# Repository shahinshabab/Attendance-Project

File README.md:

# Office fingerprint attendance

This folder is the project workspace for an **ESP32 development board (ESP-WROOM-32), R307 UART fingerprint sensor, and 1.8″ ST7735 SPI TFT display**, with a DS3231 clock. Open `Attendance.code-workspace` in VS Code or open this folder directly.

The ESP32 is the implemented board. A standard Raspberry Pi Pico has no built-in Wi-Fi and needs different firmware; the supplied ESP32 firmware must not be flashed to a Pico. Pico W is a separate Wi-Fi-capable alternative, also requiring a port.

## Your deployed server

The dashboard/API is live at **https://attendance.shahinanalytics.com**, deployed through SSH alias `Attendance-Server`. Enter this computer's `ADMIN_API_KEY` value from `.env` in the dashboard. HTTPS, authentication, and automatic service startup have been checked. See [server details](docs/SERVER.md).

The board runs in **Wi-Fi mode** and talks to that server directly (see Connection modes below). The office Wi-Fi and fingerprint enrollment are both managed from the dashboard.

The USB connection on COM3 was verified and attendance firmware was uploaded after a full original-flash backup. Event storage was initialized and verified. The sensor (1000-slot capacity) and OLED (0x3C) were detected after shared-ground correction, but subsequent checks showed intermittent/missing communication; full power-cycle and wiring inspection are pending. Staff member Shabab (EMP001) exists on the server, but fingerprint enrollment has not succeeded and no slot is assigned. The steps below also cover running an optional local development server and provisioning another board. Do not reinitialize storage during routine firmware updates.

## Start here

1. Read [the wiring guide](docs/WIRING.md) and open [the labelled wiring diagram](docs/wiring.png) ([editable SVG](docs/wiring.svg)). Wire with USB unplugged. Use GPIO numbers, not physical header positions.
2. In PowerShell, from this folder, run:

   ```powershell
   .\scripts\setup.ps1
   .\scripts\start-server.ps1
   ```

   If your shell blocks scripts, run a command with `powershell -ExecutionPolicy Bypass -File .\scripts\setup.ps1` (process-specific; no permanent system policy change needed). Setup creates `.venv`, installs dependencies, generates independent random admin/device keys in `.env`, and copies the firmware configuration. Both secret files are git-ignored.
3. Open **http://127.0.0.1:8765**. Open `.env` locally, copy the `ADMIN_API_KEY` value into the dashboard, and click Connect. Do not share that key.
4. Connect the ESP32 development board with a **USB data cable**. In a second PowerShell window:

   ```powershell
   .\scripts\device.ps1 list
   .\scripts\device.ps1 build
   .\scripts\device.ps1 upload -Port COM3
   # FIRST INSTALL ONLY: creates the event filesystem; erases pending device scans.
   .\scripts\device.ps1 init-storage -Port COM3
   .\scripts\device.ps1 status -Port COM3
   ```

   Your board was detected as **Silicon Labs CP210x, COM3** during setup. Confirm it with `list` each time; Windows can change the port number. Do not choose a Bluetooth COM port. Close any serial monitor before uploading or opening the USB bridge. Upload replaces the board's current program. If uploading stalls at Connecting, hold BOOT, tap EN, then release BOOT when writing starts. Do not run `init-storage` during normal updates; pending scans survive ordinary firmware uploads when the partition layout is unchanged.
5. Create a staff member in the dashboard, for example `EMP001`. Enroll their fingerprint into a fresh slot:

   ```powershell
   .\scripts\device.ps1 enroll -Port COM3 -Slot 1
   ```

   Follow the display/terminal prompts: place finger, remove, place the same finger again. Enrollment takes place on the sensor; it does not create a server staff record. Assign device `office-01`, slot `1`, to `EMP001` in the dashboard. Remove the finger before starting attendance. Verify that a second enrollment into an occupied slot is refused on your particular sensor before enrolling the office.
6. Start the USB bridge:

   ```powershell
   .\scripts\device.ps1 bridge -Port COM3
   ```

   Scan, then click Refresh in the dashboard. The display's **Verified** means the finger matched and the scan is saved on the device; the terminal's **Saved** means the server accepted it. There is no IN/OUT button: the server decides IN or OUT from each person's scans that day (see [operations](docs/OPERATIONS.md)).

## Connection modes

**USB to this computer:** the ESP32 uses USB serial for enrollment and attendance. `tools/device.py` synchronizes the clock and forwards queued events. The local server and bridge both need to run. The computer can also forward to your internet server:

```powershell
.\scripts\device.ps1 bridge -Port COM3 -Server https://attendance.your-domain.example
```

Use the same device ID and device key on this computer and the remote server. The bridge never uses the admin key and validates normal HTTPS certificates.

**Standalone Wi-Fi to server (current setup):** the scanner connects straight to https://attendance.shahinanalytics.com without this computer. Office Wi-Fi is entered in the dashboard (Scanner & Wi-Fi). If it stops working, turn on a phone hotspot with the fallback name/password built into the firmware; the scanner connects through it, picks up the new office Wi-Fi from the dashboard, and switches back. No firmware change is needed. Enroll staff from the dashboard (Enroll a fingerprint): the scanner shows their name and the slot is assigned automatically. USB stays available for maintenance commands. Do not run the USB attendance bridge for a Wi-Fi board. See [server setup](docs/SERVER.md) and [operations](docs/OPERATIONS.md).

## Project layout

| Path | Purpose |
| --- | --- |
| `firmware/` | PlatformIO Arduino ESP32 firmware and hardware configuration |
| `backend/` | FastAPI service, SQLite database, and local dashboard |
| `tools/device.py` | USB bridge and physical enrollment/maintenance commands |
| `tools/firmware_config.py` | Writes the Wi-Fi-mode `config.h` (device key, server URL, root CAs, fallback hotspot) |
| `scripts/` | Windows setup, build, upload, and start commands |
| `docs/` | Wiring diagram, deployment notes, API and operating limits |
| `tests/` | API authentication, retries, date handling, and bridge acknowledgment tests |
| `.env` | Local server keys/configuration, excluded from Git |
| `data/` | Local database, excluded from Git |

Run checks with `.\.venv\Scripts\python.exe -m pytest -q`. The firmware dependencies and ESP32 platform are pinned in `platformio.ini`. Python installation versions are recorded in `requirements-lock.txt` after local verification; install that file to reproduce the tested environment.

This is a working project foundation for hardware commissioning. Hardware operation, fingerprint compatibility, and internet deployment must be verified with your actual board, sensor, display, and server before office use. See [operating notes](docs/OPERATIONS.md) for clock, queue, enrollment, and reporting limits.

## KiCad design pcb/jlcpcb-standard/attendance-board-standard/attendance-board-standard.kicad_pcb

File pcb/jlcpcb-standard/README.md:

# Standard-PCBA JLCPCB variant (ESP32 placed by JLCPCB)

Same circuit, 70 x 150 mm outline, layout and GPIO map as the other boards. It uses the Economic variant's
part choices (`../jlcpcb-economic`), and JLCPCB also places the ESP32 module U1. The module
(ESP32-WROOM-32E-N4, C701341) is **Standard-only** at JLCPCB, so this board must be ordered with
**Standard PCBA**. Its ground pad is the normal library footprint (no hand-solder holes).

| Ref | Part | Note |
| --- | --- | --- |
| U1 | C701341 ESP32-WROOM-32E-N4 | placed by JLCPCB (Standard PCBA) |
| C1, C3 | C2836436 470 uF 35 V 10 x 10.2 mm | |
| LED2, LED4, LED5 | C2297 KT-0805G green (Basic) | |
| D2 | C19077408 BZT52C10 SOD-123 | |
| L2 | rotated 180 degrees | so the boost switch node routes |

You hand-solder (see `production/hand-solder.csv`): on the front the headers J5 (display), J9 (programming,
optional) and J11 (R307); on the back BT1 (CR2032 holder), J3 (LiPo) and J7 (tamper). Standard PCBA can also
assemble the back side, but that doubles the setup and stencil fees for three easy parts.

## Files

| Path | What |
| --- | --- |
| `generator/` | Copy of `../jlcpcb-economic/generator` with U1 placed (`design.HAND` empty) |
| `attendance-board-standard/` | KiCad project, schematic PDF, DRC report |
| `production/` (git-ignored) | `attendance-board-standard-gerbers.zip`, `bom.csv`, `cpl.csv`, `hand-solder.csv`, renders |

## Ordering

PCB Assembly -> **Standard**, top side only; upload `bom.csv` and `cpl.csv`; check rotations in the preview.

## Cost estimate (JLCPCB price page, updated 2026-10-22)

Standard PCBA: $25.56 setup, $8.21 stencil, $1.53 feeder loading for every BOM line (42 here), fixtures $16.42
(1-29 boards) or $24.63 (30-99), $3.58 hand-soldering labour for J1/J8, $0.0016 per SMT joint, plus parts
(about $11.20 per board with the ESP32). A handling fee of at least $14.93 may be added. Excludes the bare PCB
and shipping.

| Boards | Standard (this board) | Economic + ESP32 soldered by you (`../jlcpcb-economic`) |
| --- | --- | --- |
| 5 | ~ $177 (up to ~ $192 with handling fee) | ~ $121 |
| 10 | ~ $236 | ~ $180 |
| 30 | ~ $480 | ~ $414 |

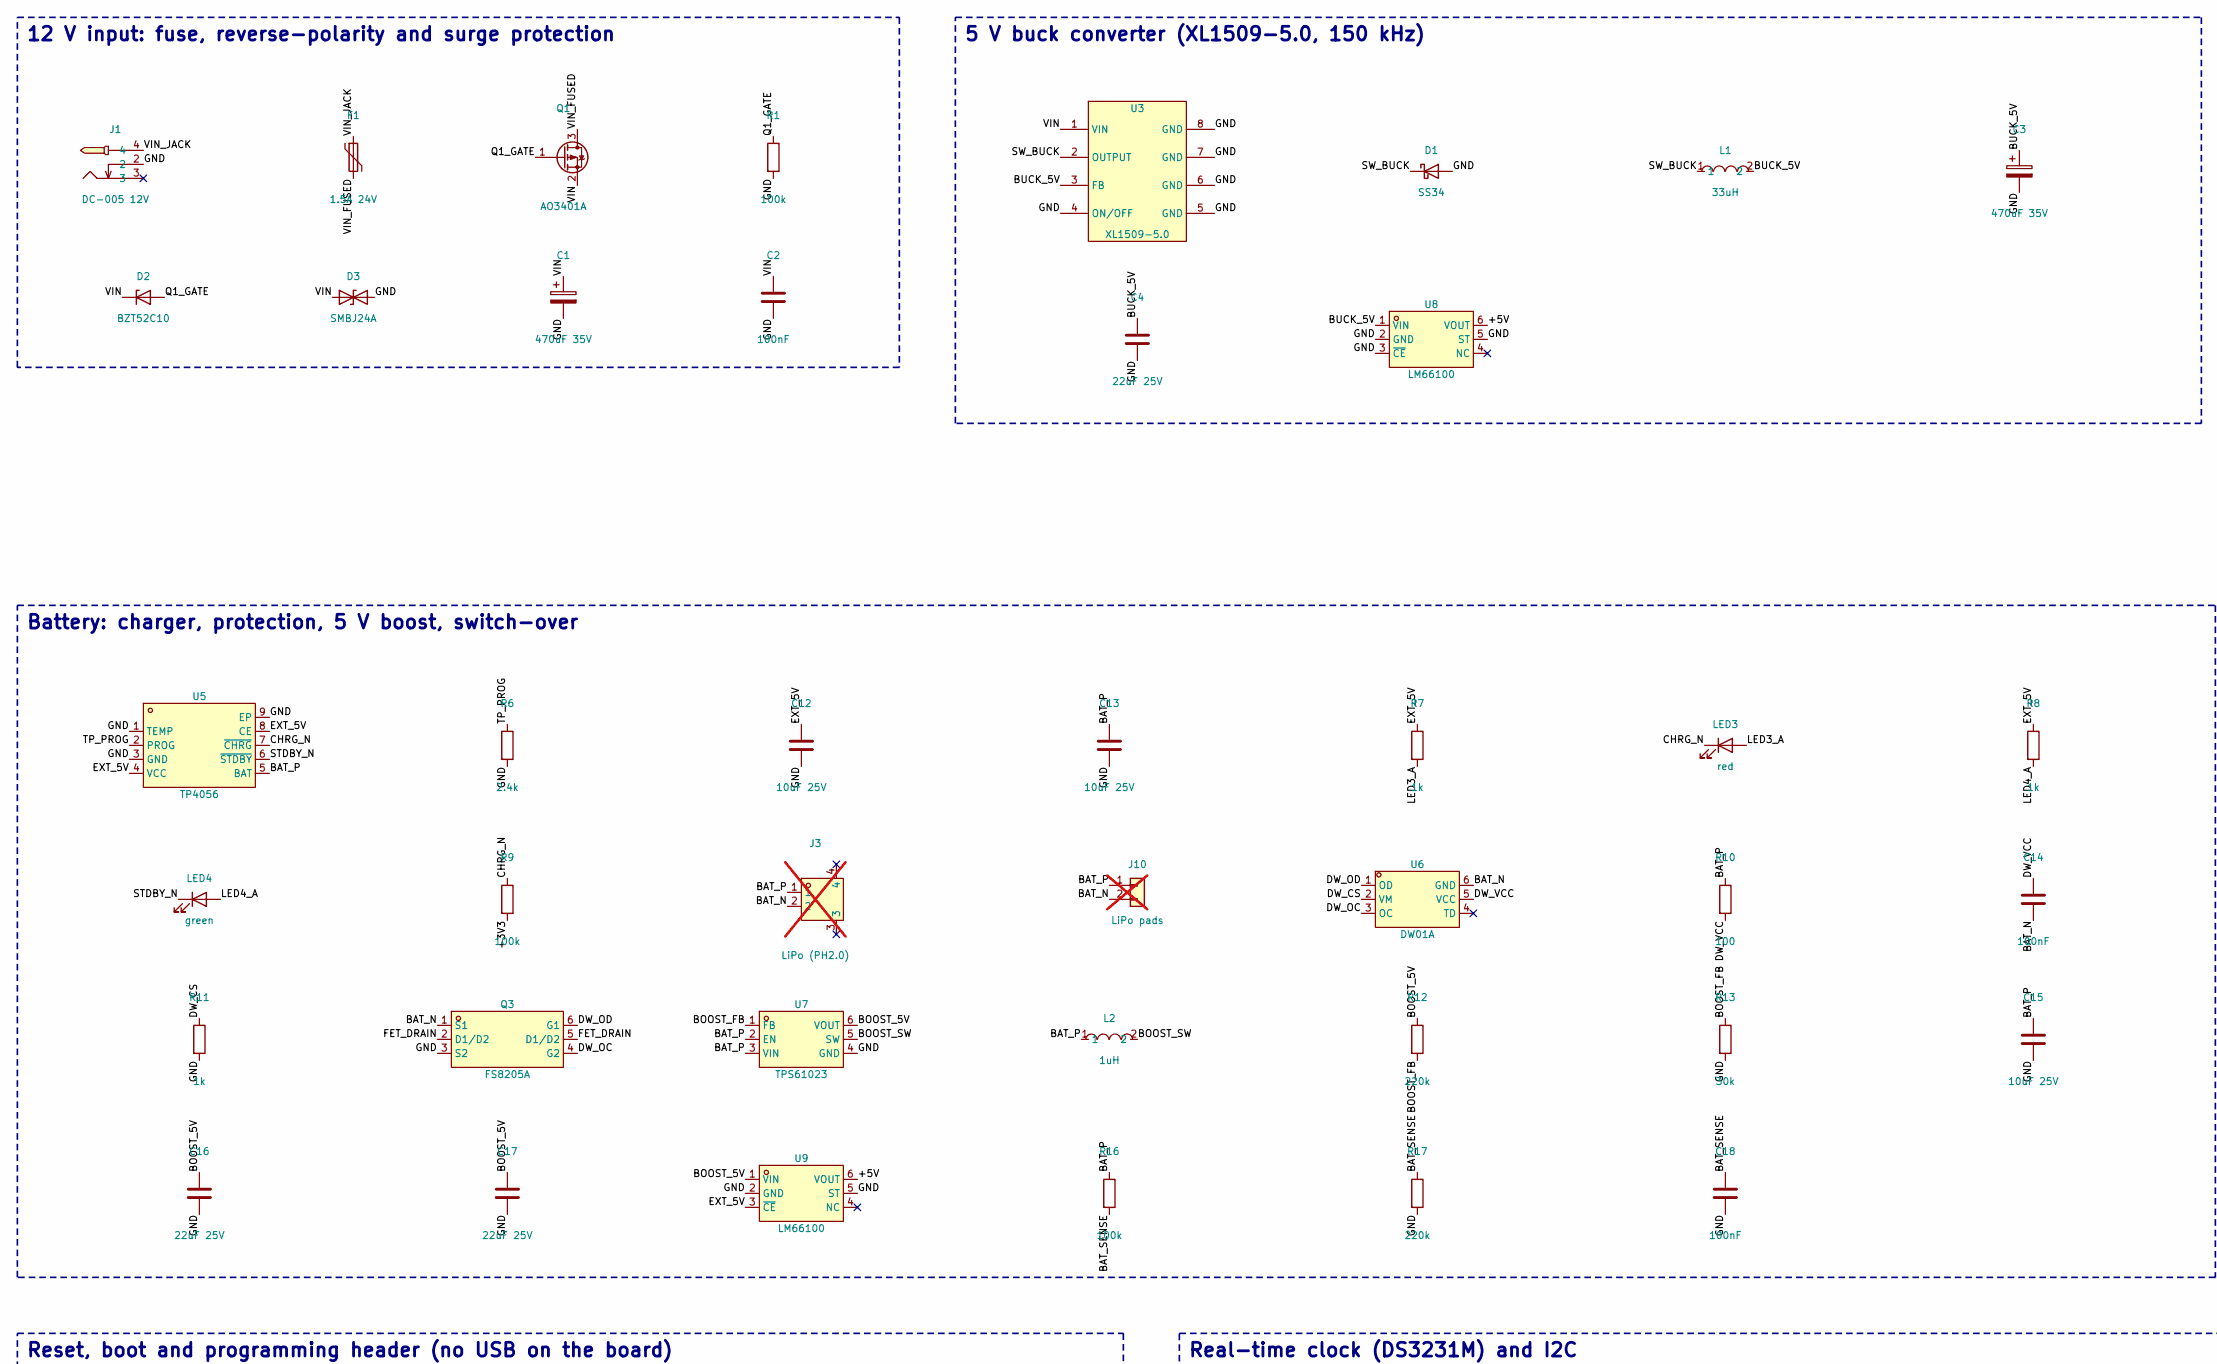
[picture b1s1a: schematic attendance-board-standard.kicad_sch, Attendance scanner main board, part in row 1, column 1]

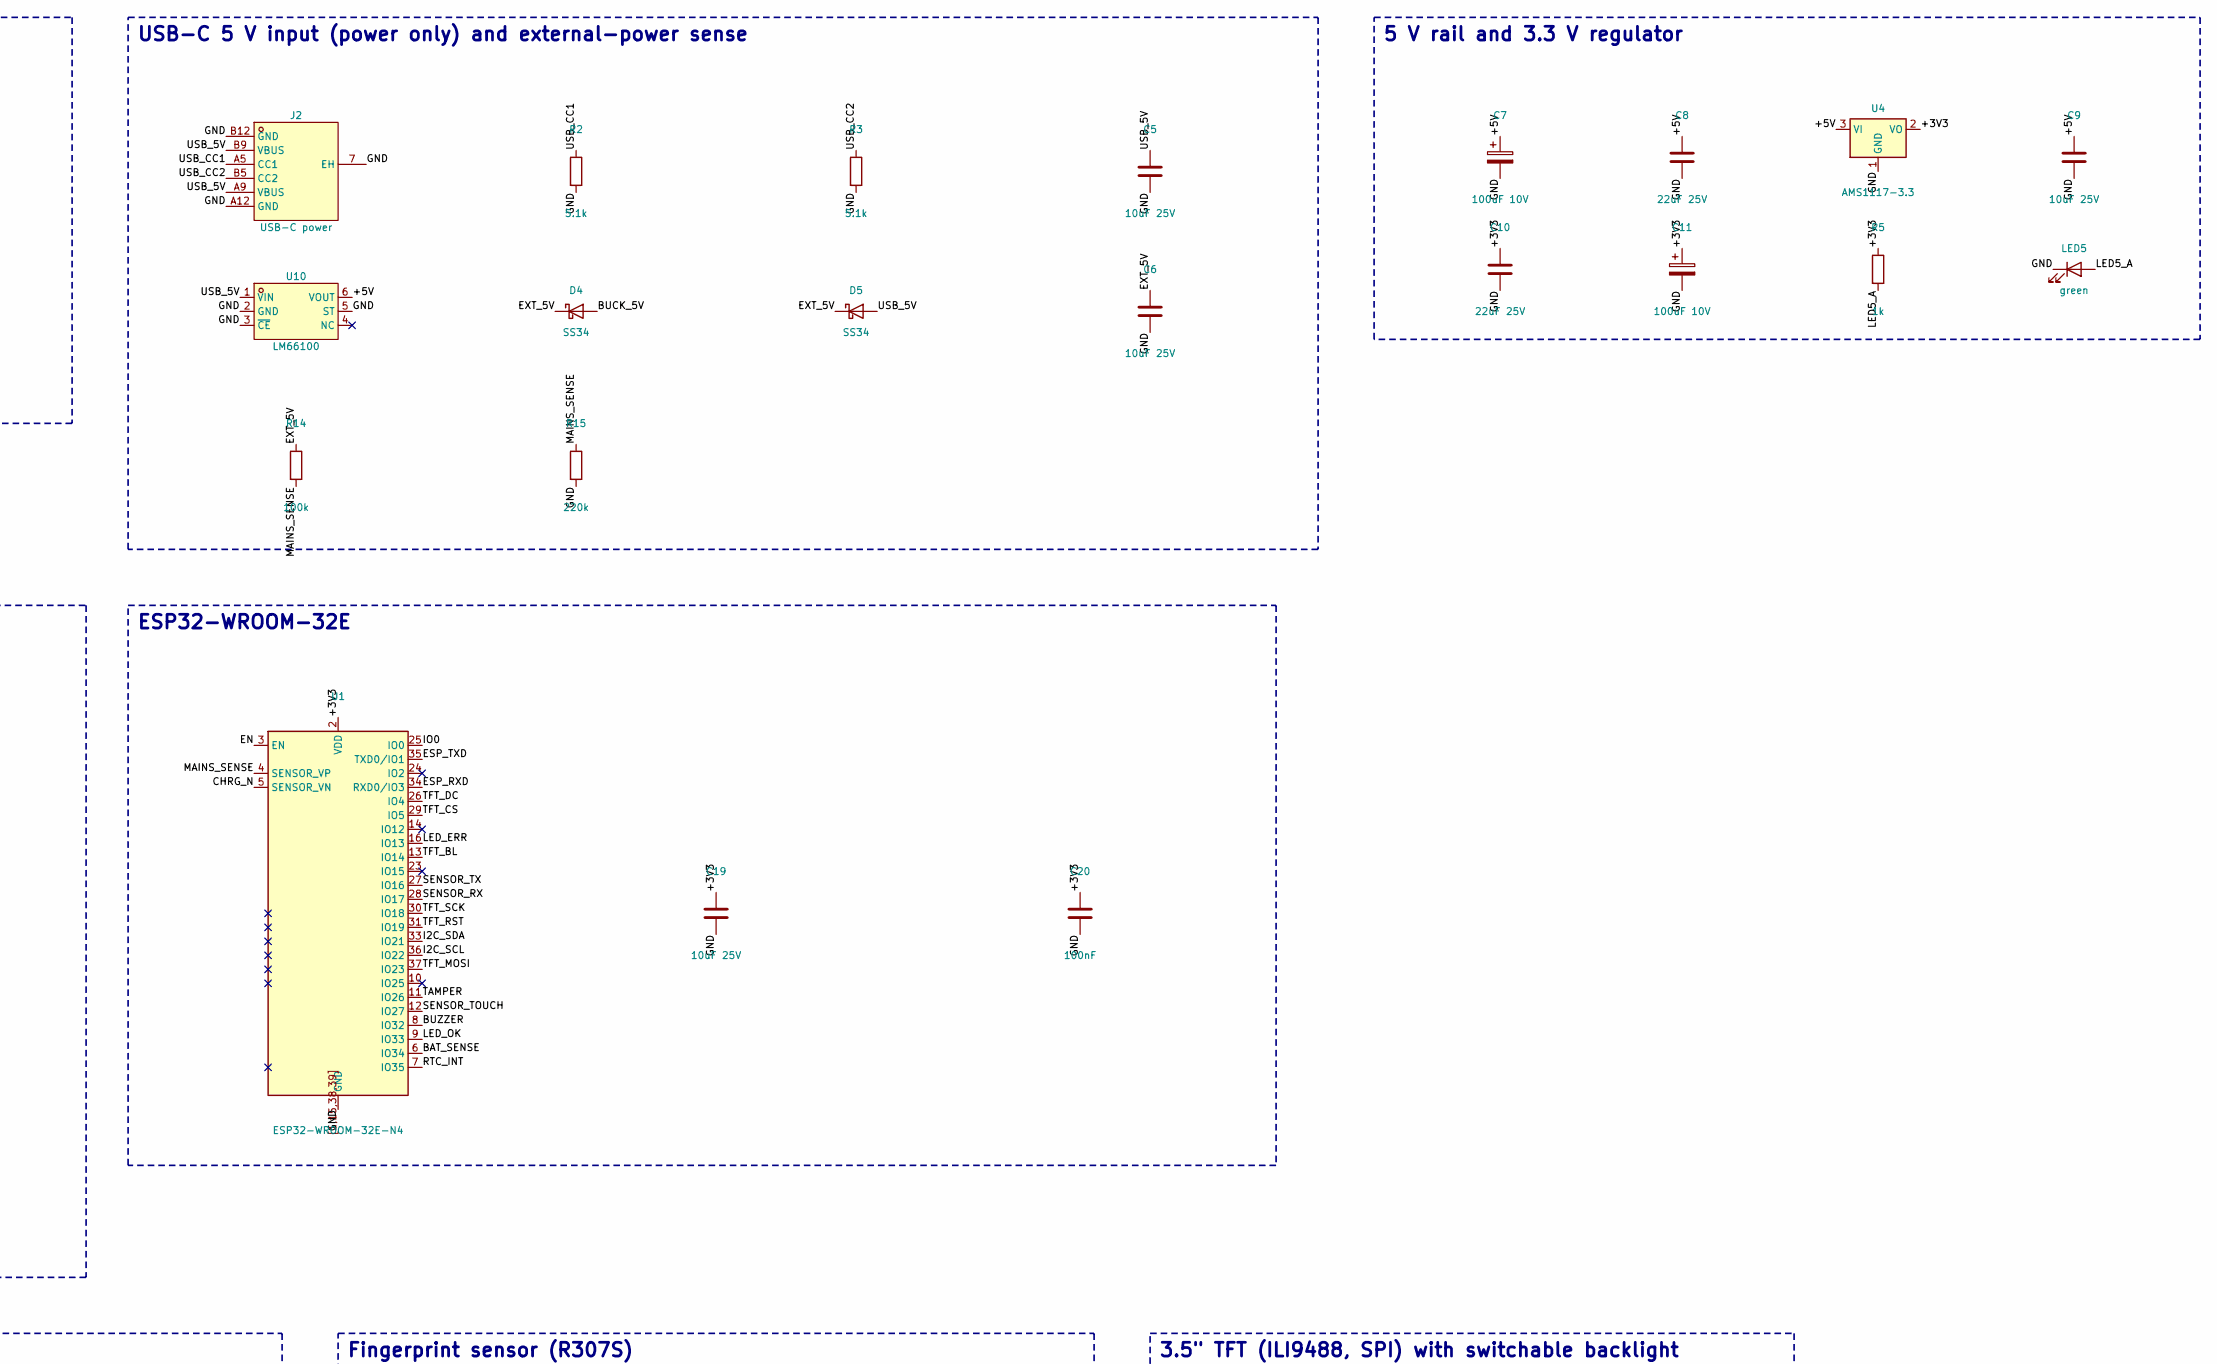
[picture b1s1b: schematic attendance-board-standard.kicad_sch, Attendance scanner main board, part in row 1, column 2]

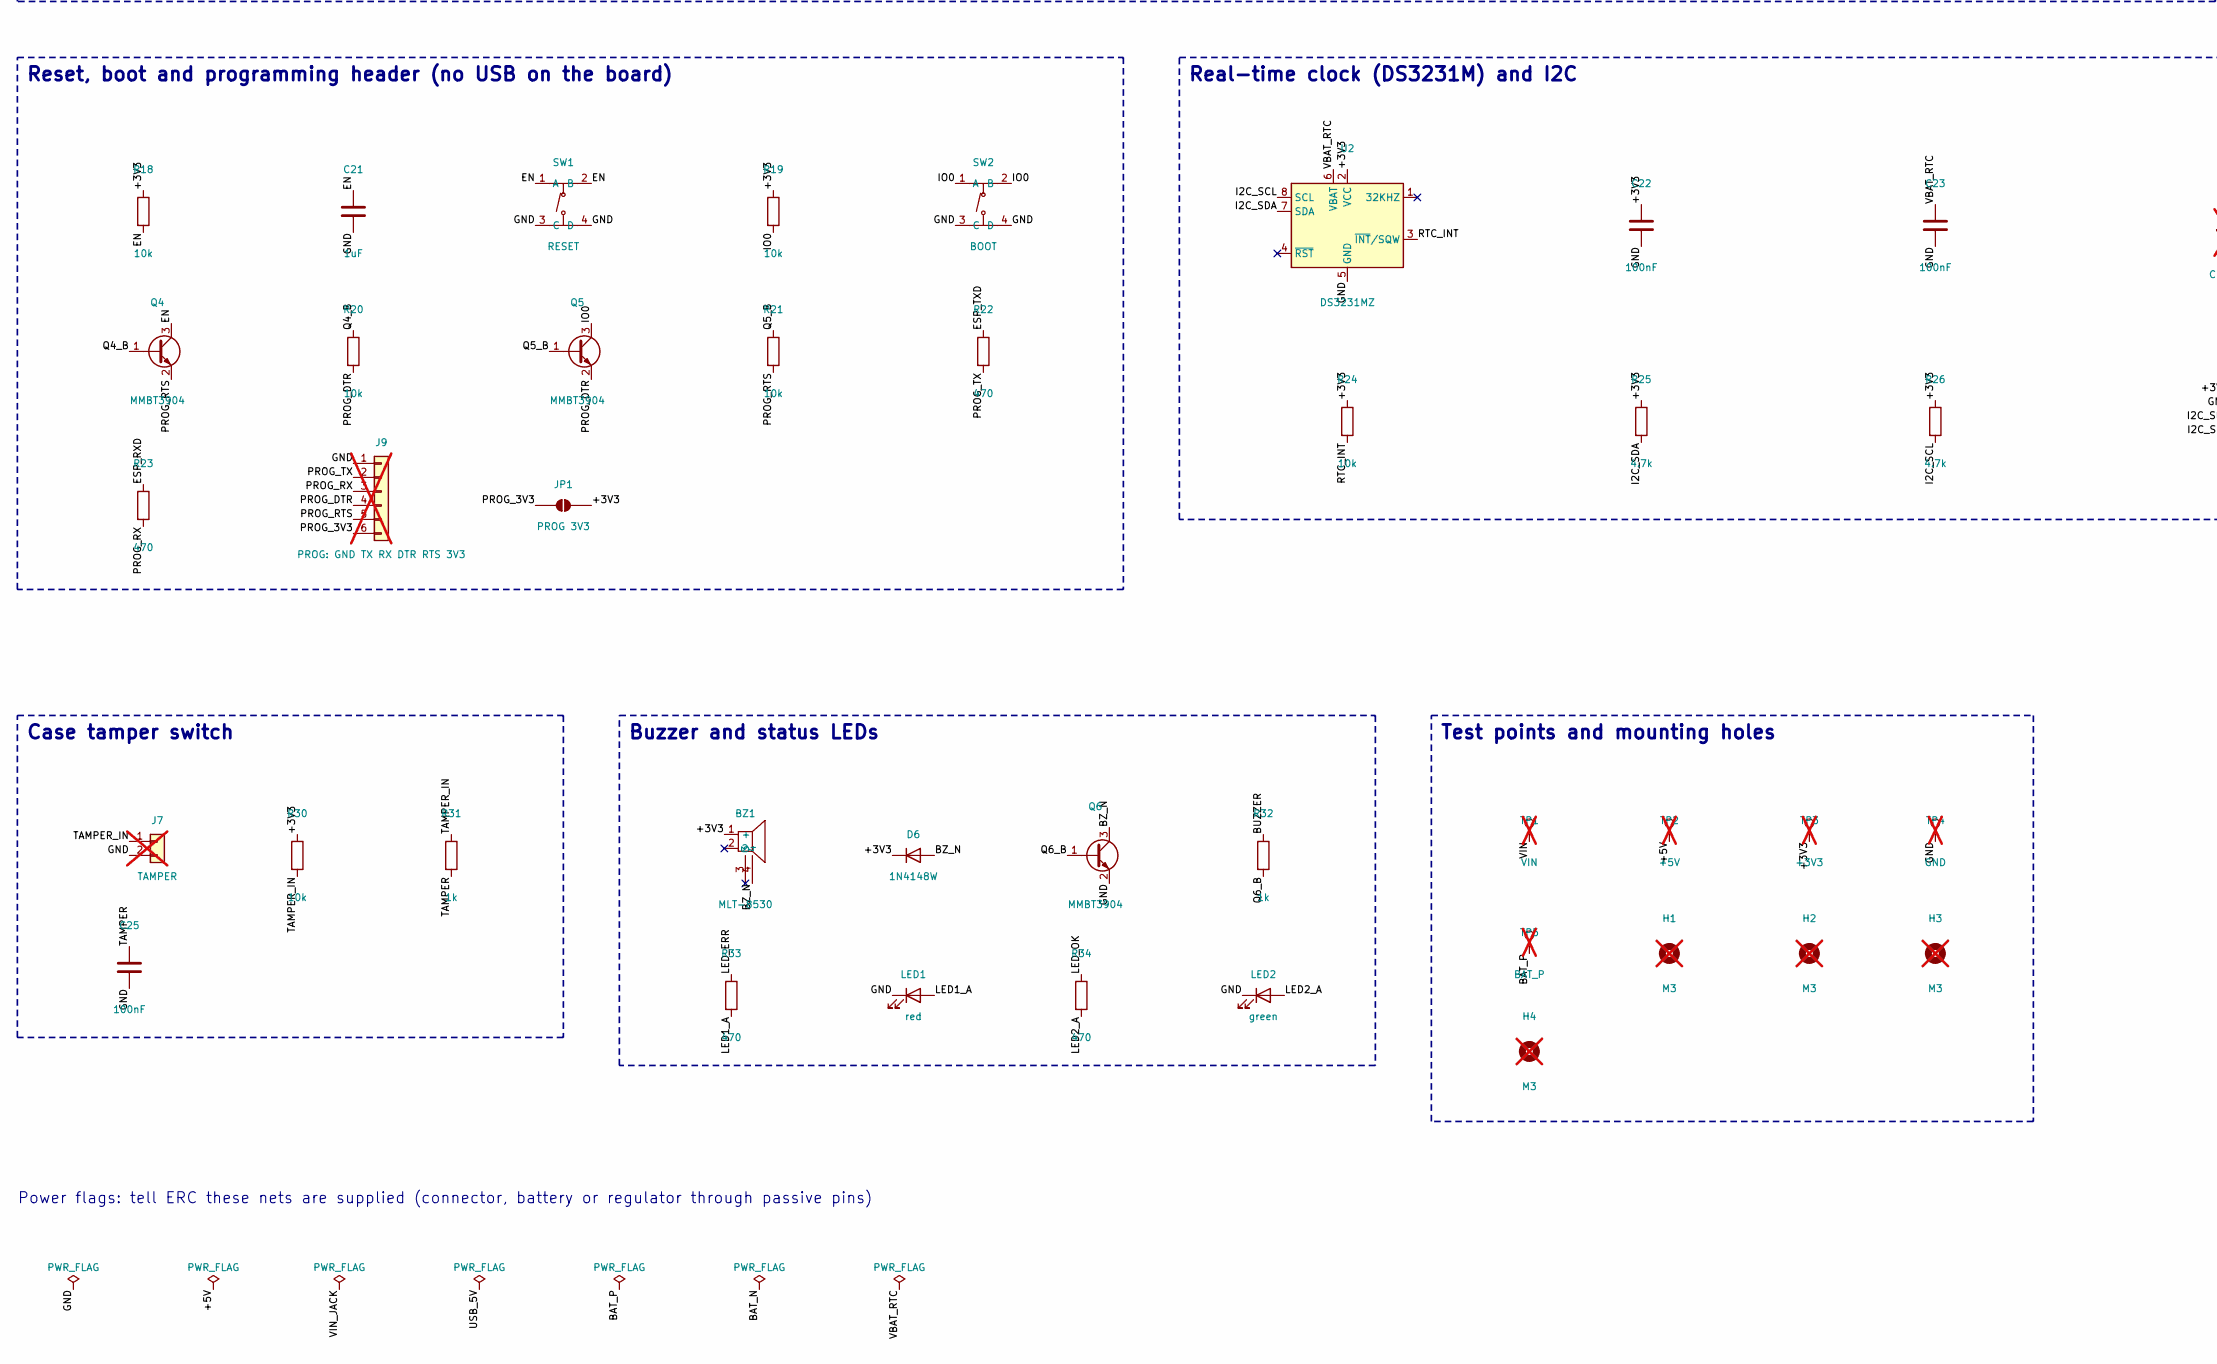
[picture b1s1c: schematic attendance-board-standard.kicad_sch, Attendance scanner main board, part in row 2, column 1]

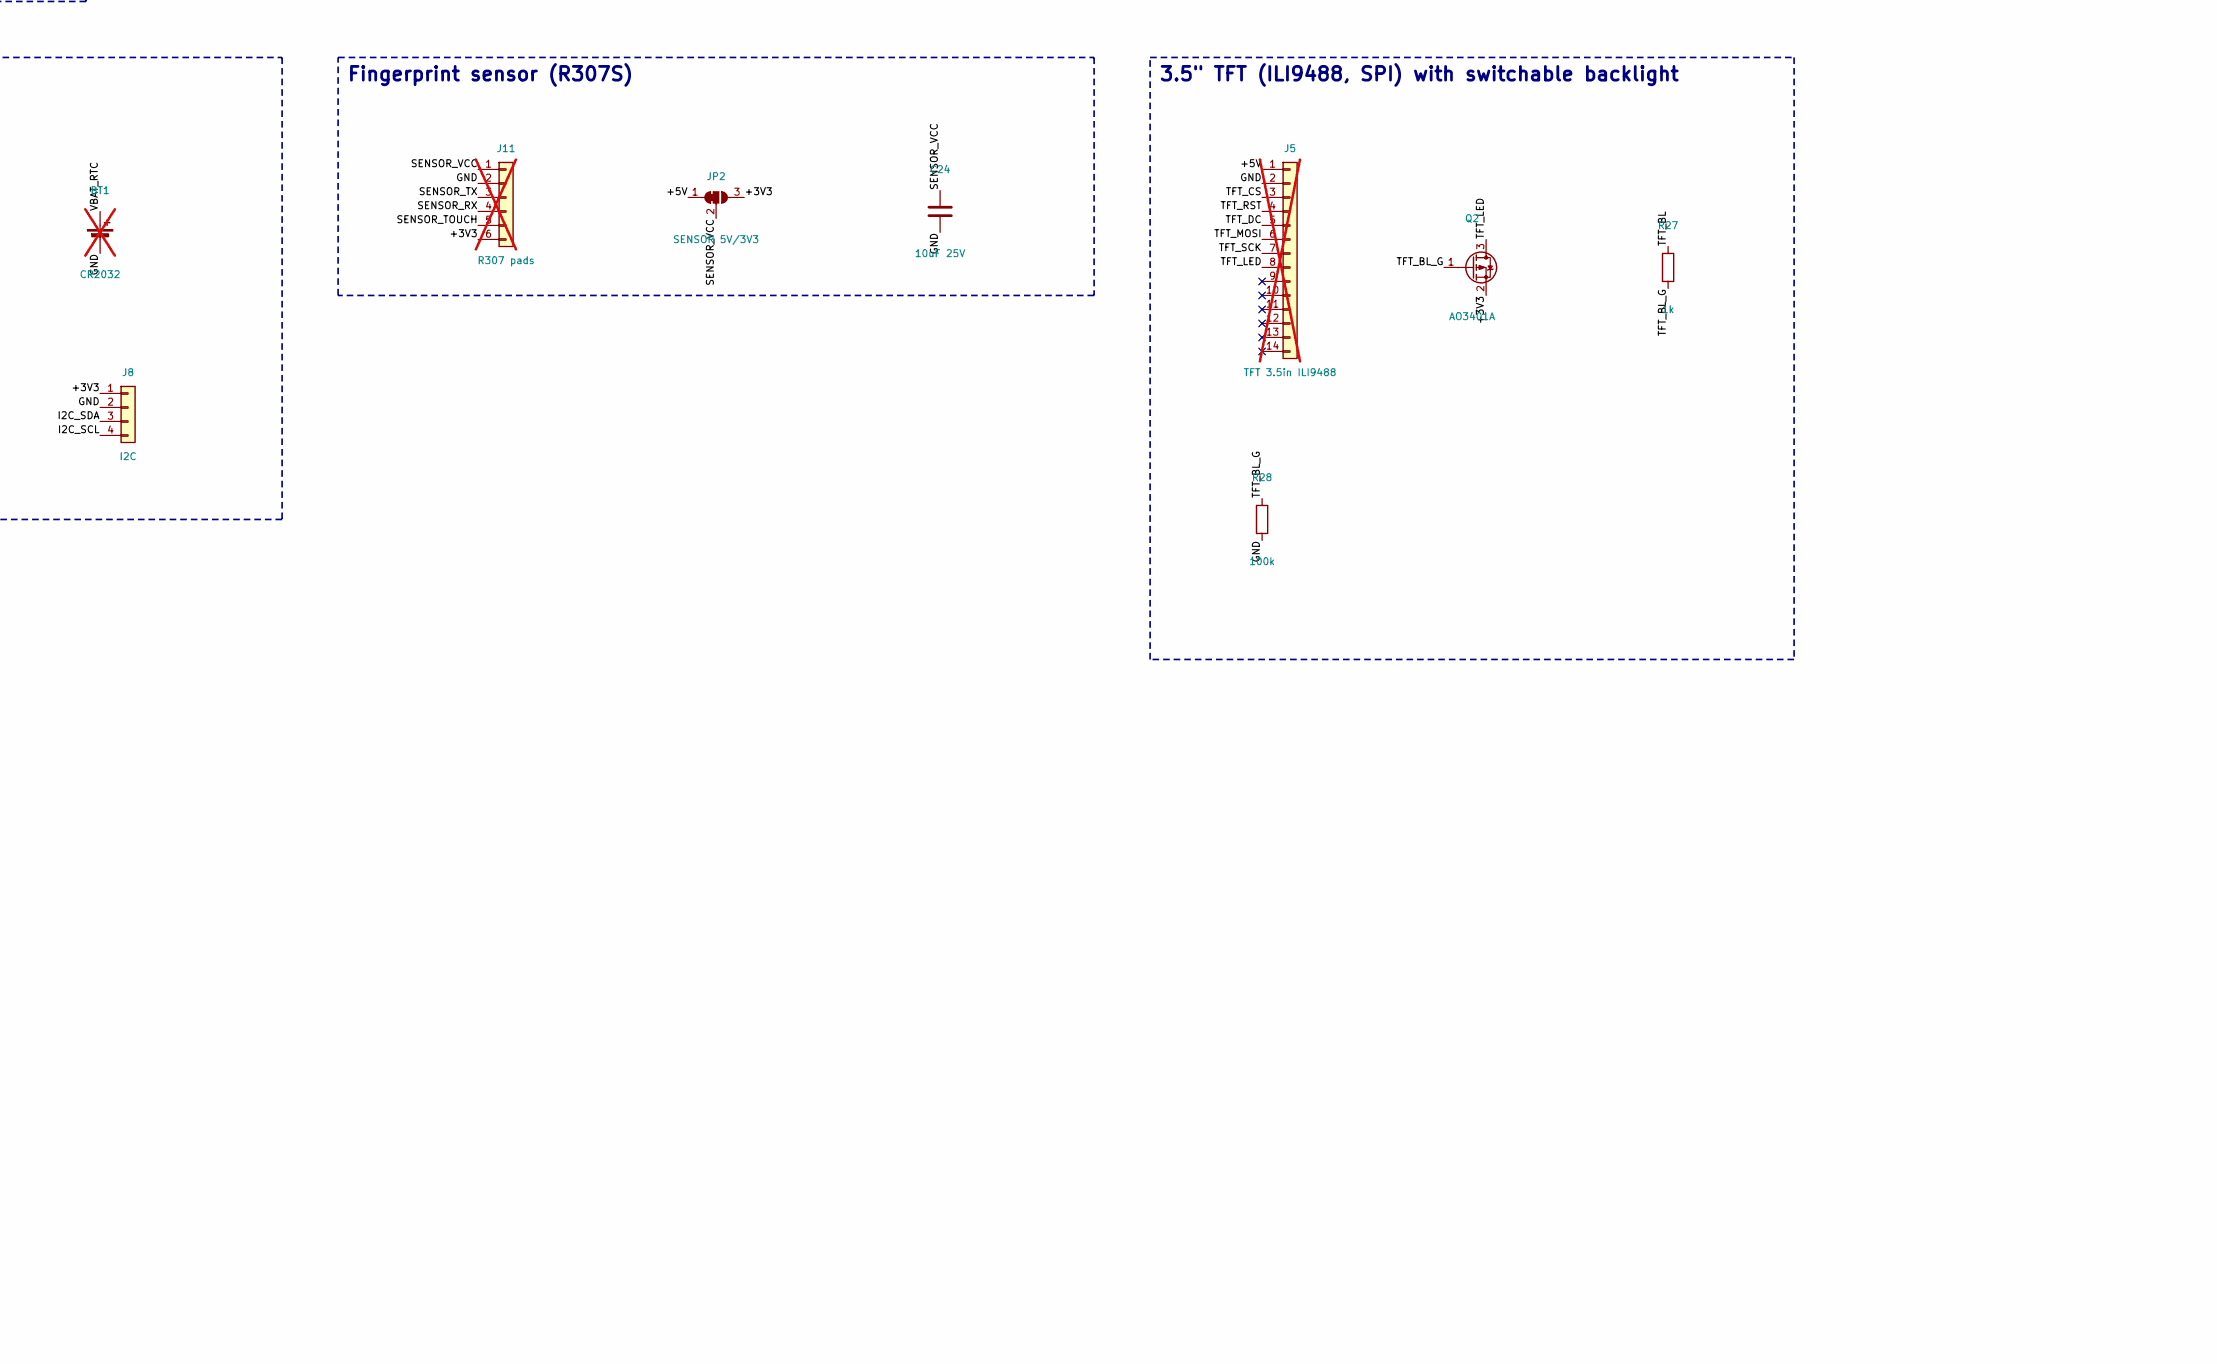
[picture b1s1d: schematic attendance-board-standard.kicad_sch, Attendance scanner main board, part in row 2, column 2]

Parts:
BT1: CR2032; BatteryHolder_Keystone_3034_1x20mm; LCSC C5213768; not fitted
BZ1: MLT-8530; BUZ-SMD_4P-L8.5-W8.5-P8.50-BR; LCSC C94599
C1, C3: 470uF 35V; CP_Elec_10x10; LCSC C2836436
C2, C14, C18, C20, C22, C23, C25: 100nF; C_0603_1608Metric; LCSC C14663
C4, C8, C10, C16, C17: 22uF 25V; C_0805_2012Metric; LCSC C45783
C5, C6, C9, C12, C13, C15, C19, C24: 10uF 25V; C_0805_2012Metric; LCSC C15850
C7, C11: 100uF 10V; CP_EIA-3528-21_Kemet-B; LCSC C129567
C21: 1uF; C_0603_1608Metric; LCSC C15849
D1, D4, D5: SS34; D_SMA; LCSC C8678
D2: BZT52C10; D_SOD-123; LCSC C19077408
D3: SMBJ24A; D_SMB; LCSC C87268
D6: 1N4148W; D_SOD-123; LCSC C81598
F1: 1.5A 24V; Fuse_1812_4532Metric; LCSC C32404
H1, H2, H3, H4: M3; MountingHole_3.2mm_M3; not fitted
J1: DC-005 12V; DC-IN-TH_DC-005-5.5-2.0; LCSC C16214
J2: USB-C power; TYPE-C-SMD_TYPE-C-6P_1; LCSC C456012
J3: LiPo (PH2.0); CONN-SMD_PH2.0-1X2PW; LCSC C722761; not fitted
J5: TFT 3.5in ILI9488; PinHeader_1x14_P2.54mm_Vertical; not fitted
J7: TAMPER; JST_XH_B2B-XH-A_1x02_P2.50mm_Vertical; LCSC C158012; not fitted
J8: I2C; JST_XH_B4B-XH-A_1x04_P2.50mm_Vertical; LCSC C144395
J9: PROG: GND TX RX DTR RTS 3V3; PinHeader_1x06_P2.54mm_Vertical; not fitted
J10: LiPo pads; SolderWire-0.5sqmm_1x02_P4.6mm_D0.9mm_OD2.1mm; not fitted
J11: R307 pads; PinHeader_1x06_P2.54mm_Vertical; not fitted
JP1: PROG 3V3; SolderJumper-2_P1.3mm_Open_RoundedPad1.0x1.5mm
JP2: SENSOR 5V/3V3; SolderJumper-3_P1.3mm_Bridged12_RoundedPad1.0x1.5mm
L1: 33uH; IND-SMD_L8.0-W8.0_FNR80XXS; LCSC C168133
L2: 1uH; IND-SMD_L4.0-W4.0_PRS4018; LCSC C96152
LED1, LED3: red; LED_0805_2012Metric; LCSC C84256
LED2, LED4, LED5: green; LED_0805_2012Metric; LCSC C2297
Q1, Q2: AO3401A; SOT-23; LCSC C15127
Q3: FS8205A; SOT-23-6_L2.9-W1.6-P0.95-LS2.8-BR; LCSC C2830320
Q4, Q5, Q6: MMBT3904; SOT-23; LCSC C20526
R1, R9, R14, R16, R28: 100k; R_0603_1608Metric; LCSC C25803
R2, R3: 5.1k; R_0603_1608Metric; LCSC C23186
R5, R7, R8, R11, R27, R31, R32: 1k; R_0603_1608Metric; LCSC C21190
R6: 2.4k; R_0603_1608Metric; LCSC C22940
R10: 100; R_0603_1608Metric; LCSC C22775
R12, R15, R17: 220k; R_0603_1608Metric; LCSC C22961
R13: 30k; R_0603_1608Metric; LCSC C22984
R18, R19, R20, R21, R24, R30: 10k; R_0603_1608Metric; LCSC C25804
R22, R23, R33, R34: 470; R_0603_1608Metric; LCSC C23179
R25, R26: 4.7k; R_0603_1608Metric; LCSC C23162
SW1: RESET; SW-SMD_4P-L5.1-W5.1-P3.70-LS6.5-TL_H1.5; LCSC C318884
SW2: BOOT; SW-SMD_4P-L5.1-W5.1-P3.70-LS6.5-TL_H1.5; LCSC C318884
TP1: VIN; TestPoint_Pad_D1.5mm; not fitted
TP2: +5V; TestPoint_Pad_D1.5mm; not fitted
TP3: +3V3; TestPoint_Pad_D1.5mm; not fitted
TP4: GND; TestPoint_Pad_D1.5mm; not fitted
TP5: BAT_P; TestPoint_Pad_D1.5mm; not fitted
U1: ESP32-WROOM-32E-N4; ESP32-WROOM-32E; LCSC C701341
U2: DS3231MZ; SOIC-8_3.9x4.9mm_P1.27mm; LCSC C107410
U3: XL1509-5.0; SOIC-8_L5.0-W4.0-P1.27-LS6.0-BL; LCSC C61063
U4: AMS1117-3.3; SOT-223-3_TabPin2; LCSC C6186
U5: TP4056; ESOP-8_L4.9-W3.9-P1.27-LS6.0-BL-EP; LCSC C725790
U6: DW01A; SOT-23-6_L2.9-W1.6-P0.95-LS2.8-BL; LCSC C351410
U7: TPS61023; SOT-563_L1.6-W1.2-P0.50-LS1.6-BR; LCSC C919459
U8, U9, U10: LM66100; SC-70-6_L2.0-W1.3-P0.65-LS2.1-BL; LCSC C2869734

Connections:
/+3V3: BZ1.1 (+), C10.1, C11.1, C19.1, C20.1, C22.1, D6.1 (K), J8.1, J11.6, JP1.2 (B), JP2.3 (B), Q2.2 (S), R5.1, R9.2, R18.1, R19.1, R24.1, R25.1, R26.1, R30.1, TP3.1, U1.2 (VDD), U2.2 (VCC), U4.2 (VO)
/+5V: C7.1, C8.1, C9.1, J5.1, JP2.1 (A), TP2.1, U4.3 (VI), U8.6 (VOUT), U9.6 (VOUT), U10.6 (VOUT)
/BAT_N: C14.2, J3.2, J10.2, Q3.1 (S1), U6.6 (GND)
/BAT_P: C13.1, C15.1, J3.1, J10.1, L2.1, R10.1, R16.1, TP5.1, U5.5 (BAT), U7.2 (EN), U7.3 (VIN)
/BAT_SENSE: C18.1, R16.2, R17.1, U1.6 (IO34)
/BOOST_5V: C16.1, C17.1, R12.1, U7.6 (VOUT), U9.1 (VIN)
/BOOST_FB: R12.2, R13.1, U7.1 (FB)
/BOOST_SW: L2.2, U7.5 (SW)
/BUCK_5V: C3.1, C4.1, D4.2 (A), L1.2, U3.3 (FB), U8.1 (VIN)
/BUZZER: R32.1, U1.8 (IO32)
/BZ_N: BZ1.4, D6.2 (A), Q6.3 (C)
/CHRG_N: LED3.1 (K), R9.1, U1.5 (SENSOR_VN), U5.7 (~CHRG)
/DW_CS: R11.1, U6.2 (VM)
/DW_OC: Q3.4 (G2), U6.3 (OC)
/DW_OD: Q3.6 (G1), U6.1 (OD)
/DW_VCC: C14.1, R10.2, U6.5 (VCC)
/EN: C21.1, Q4.3 (C), R18.2, SW1.1 (A), SW1.2 (B), U1.3 (EN)
/ESP_RXD: R23.1, U1.34 (RXD0/IO3)
/ESP_TXD: R22.1, U1.35 (TXD0/IO1)
/EXT_5V: C6.1, C12.1, D4.1 (K), D5.1 (K), R7.1, R8.1, R14.1, U5.4 (VCC), U5.8 (CE), U9.3 (~CE)
/FET_DRAIN: Q3.2 (D1/D2), Q3.5 (D1/D2)
/GND: BT1.2 (-), C1.2, C2.2, C3.2, C4.2, C5.2, C6.2, C7.2, C8.2, C9.2, C10.2, C11.2, C12.2, C13.2, C15.2, C16.2, C17.2, C18.2, C19.2, C20.2, C21.2, C22.2, C23.2, C24.2, C25.2, D1.2 (A), D3.2 (A2), J1.2, J2.7 (EH), J2.A12 (GND), J2.B12 (GND), J5.2, J7.2, J8.2, J9.1, J11.2, LED1.1 (K), LED2.1 (K), LED5.1 (K), Q3.3 (S2), Q6.2 (E), R1.2, R2.2, R3.2, R6.2, R11.2, R13.2, R15.2, R17.2, R28.2, SW1.3 (C), SW1.4 (D), SW2.3 (C), SW2.4 (D), TP4.1, U1.1, U1.15, U1.38, U1.39, U1.[1,15,38,39] (GND), U2.5 (GND), U3.4 (ON/OFF), U3.5 (GND), U3.6 (GND), U3.7 (GND), U3.8 (GND), U4.1 (GND), U5.1 (TEMP), U5.3 (GND), U5.9 (EP), U7.4 (GND), U8.2 (GND), U8.3 (~CE), U8.5 (ST), U9.2 (GND), U9.5 (ST), U10.2 (GND), U10.3 (~CE), U10.5 (ST)
/I2C_SCL: J8.4, R26.2, U1.36 (IO22), U2.8 (SCL)
/I2C_SDA: J8.3, R25.2, U1.33 (IO21), U2.7 (SDA)
/IO0: Q5.3 (C), R19.2, SW2.1 (A), SW2.2 (B), U1.25 (IO0)
/LED1_A: LED1.2 (A), R33.2
/LED2_A: LED2.2 (A), R34.2
/LED3_A: LED3.2 (A), R7.2
/LED4_A: LED4.2 (A), R8.2
/LED5_A: LED5.2 (A), R5.2
/LED_ERR: R33.1, U1.16 (IO13)
/LED_OK: R34.1, U1.9 (IO33)
/MAINS_SENSE: R14.2, R15.1, U1.4 (SENSOR_VP)
/PROG_3V3: J9.6, JP1.1 (A)
/PROG_DTR: J9.4, Q5.2 (E), R20.2
/PROG_RTS: J9.5, Q4.2 (E), R21.2
/PROG_RX: J9.3, R23.2
/PROG_TX: J9.2, R22.2
/Q1_GATE: D2.2 (A), Q1.1 (G), R1.1
/Q4_B: Q4.1 (B), R20.1
/Q5_B: Q5.1 (B), R21.1
/Q6_B: Q6.1 (B), R32.2
/RTC_INT: R24.2, U1.7 (IO35), U2.3 (~INT/SQW)
/SENSOR_RX: J11.4, U1.28 (IO17)
/SENSOR_TOUCH: J11.5, U1.12 (IO27)
/SENSOR_TX: J11.3, U1.27 (IO16)
/SENSOR_VCC: C24.1, J11.1, JP2.2 (C)
/STDBY_N: LED4.1 (K), U5.6 (~STDBY)
/SW_BUCK: D1.1 (K), L1.1, U3.2 (OUTPUT)
/TAMPER: C25.1, R31.2, U1.11 (IO26)
/TAMPER_IN: J7.1, R30.2, R31.1
/TFT_BL: R27.1, U1.13 (IO14)
/TFT_BL_G: Q2.1 (G), R27.2, R28.1
/TFT_CS: J5.3, U1.29 (IO5)
/TFT_DC: J5.5, U1.26 (IO4)
/TFT_LED: J5.8, Q2.3 (D)
/TFT_MOSI: J5.6, U1.37 (IO23)
/TFT_RST: J5.4, U1.31 (IO19)
/TFT_SCK: J5.7, U1.30 (IO18)
/TP_PROG: R6.1, U5.2 (PROG)
/USB_5V: C5.1, D5.2 (A), J2.A9 (VBUS), J2.B9 (VBUS), U10.1 (VIN)
/USB_CC1: J2.A5 (CC1), R2.1
/USB_CC2: J2.B5 (CC2), R3.1
/VBAT_RTC: BT1.1 (+), C23.1, U2.6 (VBAT)
/VIN: C1.1, C2.1, D2.1 (K), D3.1 (A1), Q1.2 (S), TP1.1, U3.1 (VIN)
/VIN_FUSED: F1.2, Q1.3 (D)
/VIN_JACK: F1.1, J1.4

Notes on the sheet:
12 V input: fuse, reverse-polarity and surge protection
5 V buck converter (XL1509-5.0, 150 kHz)
USB-C 5 V input (power only) and external-power sense
5 V rail and 3.3 V regulator
Battery: charger, protection, 5 V boost, switch-over
ESP32-WROOM-32E
Reset, boot and programming header (no USB on the board)
Real-time clock (DS3231M) and I2C
Fingerprint sensor (R307S)
3.5" TFT (ILI9488, SPI) with switchable backlight
Case tamper switch
Buzzer and status LEDs
Test points and mounting holes
Power flags: tell ERC these nets are supplied (connector, battery or regulator through passive pins)

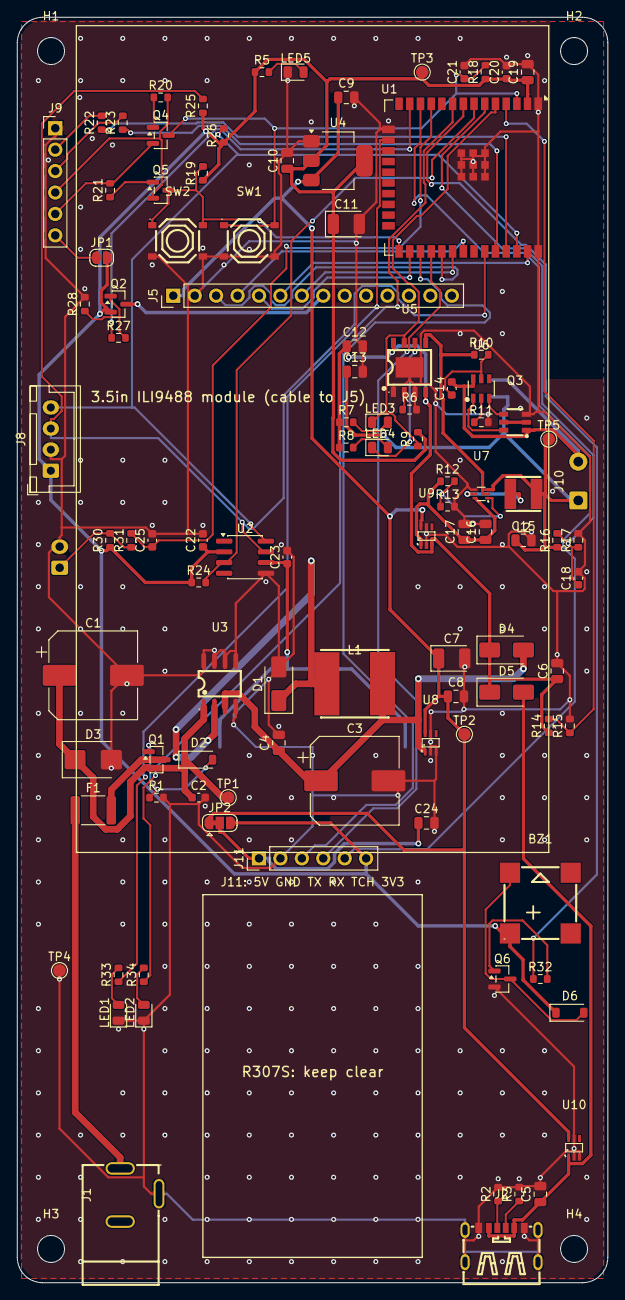
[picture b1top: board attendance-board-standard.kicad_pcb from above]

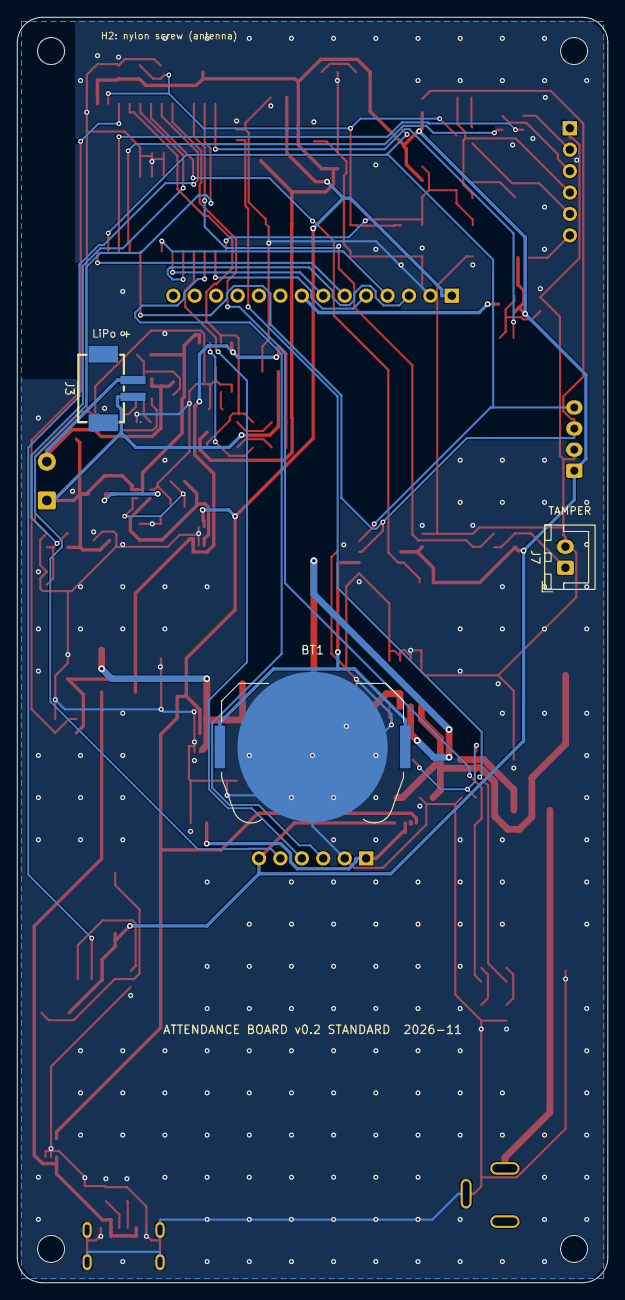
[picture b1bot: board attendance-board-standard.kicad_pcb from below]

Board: 2 copper layers, 70.0 x 150.0 mm, 111 parts (3 on the bottom side), 67 nets.

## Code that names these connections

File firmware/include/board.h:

#pragma once
// Hardware variant: pins and display. Chosen by the PlatformIO environment (build flags), never by
// config.h, which only holds this device's identity and network secrets.
//   esp32dev / esp32-st7735   ESP32 DevKit or bare ESP-WROOM-32, 1.8" ST7735 (default)
//   esp32-ili9488             same wiring, 3.5" ILI9488 SPI module
//   board-ili9488             the main PCB (ESP32-WROOM-32E) with the 3.5" ILI9488; -D BOARD_MAIN
//   nodemcu                   temporary NodeMCU ESP8266 with the 128x64 I2C OLED
#include <Arduino.h>

#if !defined(CONFIG_H_VERSION) || CONFIG_H_VERSION < 2
#error "firmware/include/config.h is from an older version (it still holds pins). Regenerate it with: .venv\\Scripts\\python.exe -m tools.firmware_config  (keeps the hotspot password; the device key comes from .env)"
#endif

#if defined(ESP8266)
#define DISPLAY_OLED 1
constexpr char HARDWARE_NAME[] = "nodemcu-oled";
// NodeMCU ESP8266: GPIO numbers, NodeMCU label in brackets. Sensor uses software serial.
constexpr int SENSOR_RX = 14; // [D5] ESP RX <- R307 TX
constexpr int SENSOR_TX = 12; // [D6] ESP TX -> R307 RX
constexpr int I2C_SDA = 4;    // [D2]
constexpr int I2C_SCL = 5;    // [D1]
constexpr int FINGER_TOUCH_PIN = -1; // no spare pin: poll the sensor
constexpr uint8_t TFT_ROTATION = 0, TFT_TAB = 0; // unused: this build drives the OLED
constexpr int BUZZER_PIN = -1; // no spare pin
constexpr unsigned MAX_PENDING_EVENTS = 150; // limited RAM

#else
#if !defined(DISPLAY_ST7735) && !defined(DISPLAY_ILI9488)
#define DISPLAY_ST7735 1
#endif
#if defined(DISPLAY_ST7735) && defined(DISPLAY_ILI9488)
#error "Choose one display: DISPLAY_ST7735 or DISPLAY_ILI9488"
#endif
// Same GPIOs on the DevKit wiring (docs/WIRING.md) and the main PCB (pcb/generator/design.py).
constexpr int SENSOR_RX = 16; // ESP RX <- R307 TX
constexpr int SENSOR_TX = 17; // ESP TX -> R307 RX
constexpr int I2C_SDA = 21;   // I2C bus: DS3231 clock (0x68)
constexpr int I2C_SCL = 22;
// R307 "Touch" (finger-detect) output. The sensor is only read while a finger touches it, so its
// light stays off when idle. Polarity is detected at boot; if the wire is absent the firmware polls.
constexpr int FINGER_TOUCH_PIN = 27;
// TFT on the hardware SPI bus: SCK = IO18, MOSI (SDA/SDI) = IO23. MISO and the touch pins are unused.
constexpr int TFT_SCK = 18;
constexpr int TFT_MOSI = 23;
constexpr int TFT_CS = 5;
constexpr int TFT_DC = 4;   // labelled A0, DC or RS on the module
constexpr int TFT_RST = 19;
// Orientation and controller variant, changeable over USB without rebuilding (TFTROT n / TFTTAB n).
// ST7735: rotation 0 or 2 is portrait; TFTTAB 0 green tab, 1 red tab, 2 black tab.
// ILI9488: rotation 0 or 2 is portrait; TFTTAB 0 normal colours, 1 inverted (IPS panels).
constexpr uint8_t TFT_ROTATION = 0;
#if defined(DISPLAY_ST7735)
constexpr uint8_t TFT_TAB = 2;
#else
constexpr uint8_t TFT_TAB = 0;
#endif
// Buzzer switched by an NPN transistor: HIGH = sound. The DevKit prototype uses an active TMB12A05,
// the main PCB a passive MLT-8530; both sound with the PWM tone in main.cpp.
constexpr int BUZZER_PIN = 32;
constexpr unsigned MAX_PENDING_EVENTS = 500;

#if defined(BOARD_MAIN)
#if !defined(DISPLAY_ILI9488)
#error "The main PCB is built for the 3.5\" ILI9488 only"
#endif
constexpr char HARDWARE_NAME[] = "board-ili9488";
// Main PCB extras (pcb/generator/design.py, ESP32-WROOM-32E)
constexpr int LED_OK_PIN = 33;        // green status LED, HIGH = on
constexpr int LED_ERR_PIN = 13;       // red status LED, HIGH = on
constexpr int TFT_BL_PIN = 14;        // P-MOSFET backlight switch: LOW = on, HIGH = off (pulled on by default)
constexpr int TAMPER_PIN = 26;        // case switch: LOW = case closed (10k pull-up on the board)
constexpr int RTC_INT_PIN = 35;       // DS3231 INT/SQW, open drain, input only
constexpr int BAT_SENSE_PIN = 34;     // battery through 100k/220k: Vbat = Vadc * 320 / 220
constexpr int MAINS_SENSE_PIN = 36;   // EXT_5V through 100k/220k: about 3.4 V when external power is present
constexpr int CHRG_PIN = 39;          // TP4056 CHRG: LOW = charging
#else
constexpr char HARDWARE_NAME[] =
#if defined(DISPLAY_ST7735)
    "esp32-st7735";
#else
    "esp32-ili9488";
#endif
#endif
#endif

constexpr unsigned long SENSOR_BAUD = 57600;
